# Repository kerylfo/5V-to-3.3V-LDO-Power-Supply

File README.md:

# 5V to 3.3V LDO Power Supply Module (LT1117)

A compact, 5V-to-3.3V linear regulator PCB designed in KiCad, validated with LTspice, and optimized for thermal and EMI performance.

## Specifications
* **Input Voltage:** 5.0V
* **Output Voltage:** 3.3V DC
* **Regulator:** LT1117-3.3 (SOT-223)
* **Power Trace Width:** 0.2 mm
* **Grounding:** Continuous bottom ground plane (`B.Cu`) with low-impedance via stitching

## Bill of Materials
| Ref | Qty | Part | Footprint |
| :--- | :--- | :--- | :--- |
| U1 | 1 | LT1117-3.3 | SOT-223 |
| C1, C2 | 2 | 10µF Capacitor | 0805 |
| R1 | 1 | 330Ω Resistor | 0805 |

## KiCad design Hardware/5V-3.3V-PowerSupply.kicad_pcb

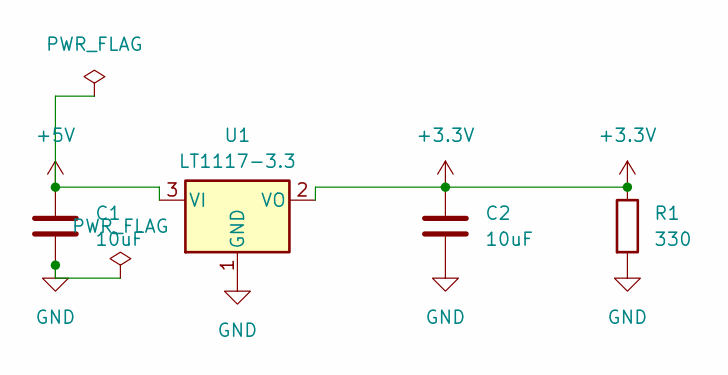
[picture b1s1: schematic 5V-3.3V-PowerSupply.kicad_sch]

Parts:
C1, C2: 10uF; C_0805_2012Metric
R1: 330; R_0805_2012Metric
U1: LT1117-3.3; SOT-223-3_TabPin2

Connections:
+3.3V: C2.1, R1.1, U1.2 (VO)
+5V: C1.1, U1.3 (VI)
GND: C1.2, C2.2, R1.2, U1.1 (GND)

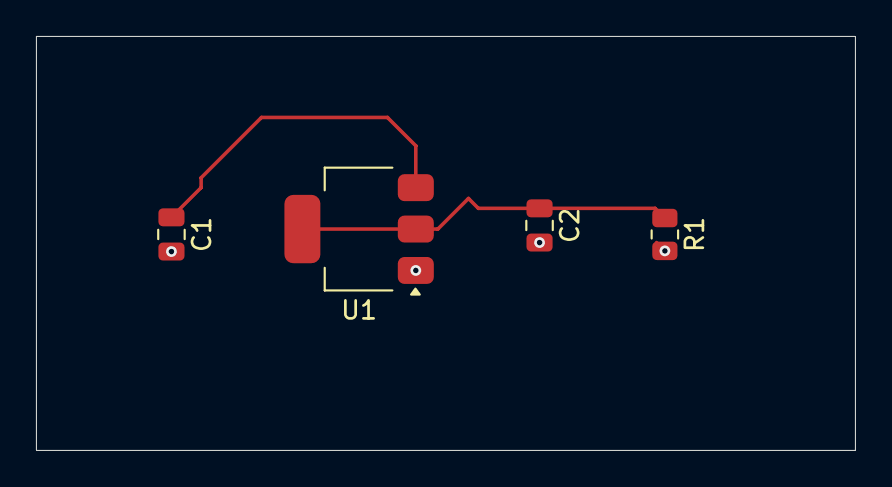
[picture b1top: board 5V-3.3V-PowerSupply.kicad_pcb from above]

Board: 2 copper layers, 45.5 x 23.0 mm, 4 parts (0 on the bottom side), 3 nets.
